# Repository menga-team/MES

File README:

1.  Clone the repository with submodules:
    SSH:
        $ git clone --recursive git@github.com:menga-team/MES.git
    HTTPS:
        $ git clone --recursive https://github.com/menga-team/MES.git
    If you already cloned the repository you can initialize the submodules with following command:
        $ git submodule update --init

2. Make libopencm3:
    $ cd libopencm3
    $ make

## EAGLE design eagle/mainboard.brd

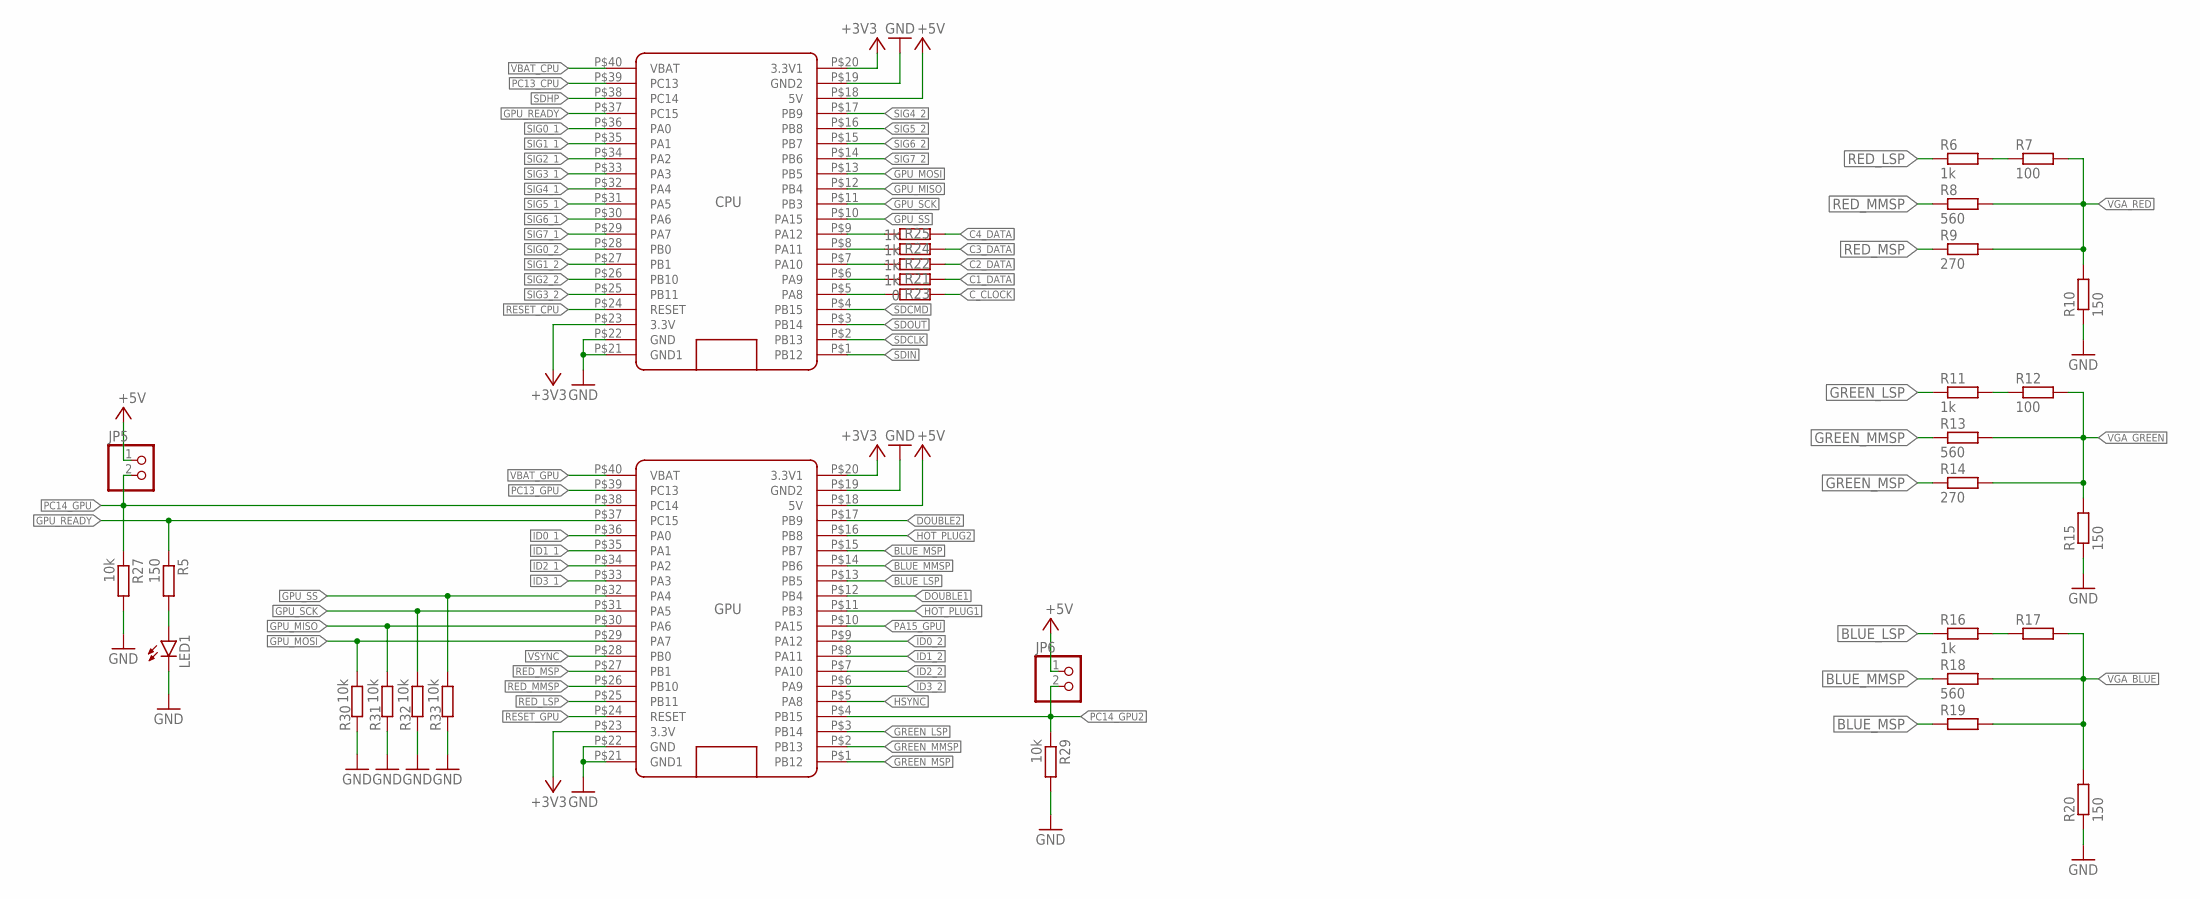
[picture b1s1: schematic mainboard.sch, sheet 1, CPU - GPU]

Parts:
CPU: BLUE_PILLADVANCED; BLUE_PILL_ADV
GPU: BLUE_PILLADVANCED; BLUE_PILL_ADV
JP5, JP6: PINHD-1X2; 1X02
LED1: LEDCHIPLED_0805; CHIPLED_0805
R5, R10, R15, R20: 150; R0805
R6, R11, R16, R21, R22, R24, R25: 1k; R0805
R7, R12, R17: 100; R0805
R8, R13, R18: 560; R0805
R9, R14, R19: 270; R0805
R23: 0; R0805
R27, R29, R30, R31, R32, R33: 10k; R0805

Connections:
+3V3: CPU.P$20 (3.3V1), CPU.P$23 (3.3V), GPU.P$20 (3.3V1), GPU.P$23 (3.3V); also elsewhere on the board
+5V: CPU.P$18 (5V), GPU.P$18 (5V), JP5.1, JP6.1; also elsewhere on the board
BLUE_LSP: GPU.P$13 (PB5), R16.1
BLUE_MMSP: GPU.P$14 (PB6), R18.1
BLUE_MSP: GPU.P$15 (PB7), R19.1
C1_DATA: R21.1; also elsewhere on the board
C2_DATA: R22.1; also elsewhere on the board
C3_DATA: R24.1; also elsewhere on the board
C4_DATA: R25.1; also elsewhere on the board
C_CLOCK: R23.1; also elsewhere on the board
DOUBLE1: GPU.P$12 (PB4); also elsewhere on the board
DOUBLE2: GPU.P$17 (PB9); also elsewhere on the board
GND: CPU.P$19 (GND2), CPU.P$21 (GND1), CPU.P$22 (GND), GPU.P$19 (GND2), GPU.P$21 (GND1), GPU.P$22 (GND), LED1.C, R10.1, R15.1, R20.1, R27.2, R29.2, R30.2, R31.2, R32.2, R33.2; also elsewhere on the board
GPU_MISO: CPU.P$12 (PB4), GPU.P$30 (PA6), R31.1
GPU_MOSI: CPU.P$13 (PB5), GPU.P$29 (PA7), R30.1
GPU_READY: CPU.P$37 (PC15), GPU.P$37 (PC15), R5.1
GPU_SCK: CPU.P$11 (PB3), GPU.P$31 (PA5), R32.1
GPU_SS: CPU.P$10 (PA15), GPU.P$32 (PA4), R33.1
GREEN_LSP: GPU.P$3 (PB14), R11.1
GREEN_MMSP: GPU.P$2 (PB13), R13.1
GREEN_MSP: GPU.P$1 (PB12), R14.1
HOT_PLUG1: GPU.P$11 (PB3); also elsewhere on the board
HOT_PLUG2: GPU.P$16 (PB8); also elsewhere on the board
HSYNC: GPU.P$5 (PA8); also elsewhere on the board
ID0_1: GPU.P$36 (PA0); also elsewhere on the board
ID0_2: GPU.P$9 (PA12); also elsewhere on the board
ID1_1: GPU.P$35 (PA1); also elsewhere on the board
ID1_2: GPU.P$8 (PA11); also elsewhere on the board
ID2_1: GPU.P$34 (PA2); also elsewhere on the board
ID2_2: GPU.P$7 (PA10); also elsewhere on the board
ID3_1: GPU.P$33 (PA3); also elsewhere on the board
ID3_2: GPU.P$6 (PA9); also elsewhere on the board
unnamed: LED1.A, R5.2
unnamed: R6.2, R7.1
unnamed: R11.2, R12.1
unnamed: R16.2, R17.1
PA8_CPU: CPU.P$5 (PA8), R23.2
PA9_CPU: CPU.P$6 (PA9), R21.2
PA9_CPU1: CPU.P$8 (PA11), R24.2
PA10_CPU: CPU.P$7 (PA10), R22.2
PA10_CPU1: CPU.P$9 (PA12), R25.2
PA15_GPU: GPU.P$10 (PA15)
PC13_CPU: CPU.P$39 (PC13)
PC13_GPU: GPU.P$39 (PC13)
PC14_GPU: GPU.P$38 (PC14), JP5.2, R27.1
PC14_GPU2: GPU.P$4 (PB15), JP6.2, R29.1
RED_LSP: GPU.P$25 (PB11), R6.1
RED_MMSP: GPU.P$26 (PB10), R8.1
RED_MSP: GPU.P$27 (PB1), R9.1
RESET_CPU: CPU.P$24 (RESET)
RESET_GPU: GPU.P$24 (RESET)
SDCLK: CPU.P$2 (PB13); also elsewhere on the board
SDCMD: CPU.P$4 (PB15); also elsewhere on the board
SDHP: CPU.P$38 (PC14); also elsewhere on the board
SDIN: CPU.P$1 (PB12); also elsewhere on the board
SDOUT: CPU.P$3 (PB14); also elsewhere on the board
SIG0_1: CPU.P$36 (PA0); also elsewhere on the board
SIG0_2: CPU.P$28 (PB0); also elsewhere on the board
SIG1_1: CPU.P$35 (PA1); also elsewhere on the board
SIG1_2: CPU.P$27 (PB1); also elsewhere on the board
SIG2_1: CPU.P$34 (PA2); also elsewhere on the board
SIG2_2: CPU.P$26 (PB10); also elsewhere on the board
SIG3_1: CPU.P$33 (PA3); also elsewhere on the board
SIG3_2: CPU.P$25 (PB11); also elsewhere on the board
SIG4_1: CPU.P$32 (PA4); also elsewhere on the board
SIG4_2: CPU.P$17 (PB9); also elsewhere on the board
SIG5_1: CPU.P$31 (PA5); also elsewhere on the board
SIG5_2: CPU.P$16 (PB8); also elsewhere on the board
SIG6_1: CPU.P$30 (PA6); also elsewhere on the board
SIG6_2: CPU.P$15 (PB7); also elsewhere on the board
SIG7_1: CPU.P$29 (PA7); also elsewhere on the board
SIG7_2: CPU.P$14 (PB6); also elsewhere on the board
VBAT_CPU: CPU.P$40 (VBAT)
VBAT_GPU: GPU.P$40 (VBAT)
VGA_BLUE: R17.2, R18.2, R19.2, R20.2; also elsewhere on the board
VGA_GREEN: R12.2, R13.2, R14.2, R15.2; also elsewhere on the board
VGA_RED: R7.2, R8.2, R9.2, R10.2; also elsewhere on the board
VSYNC: GPU.P$28 (PB0); also elsewhere on the board

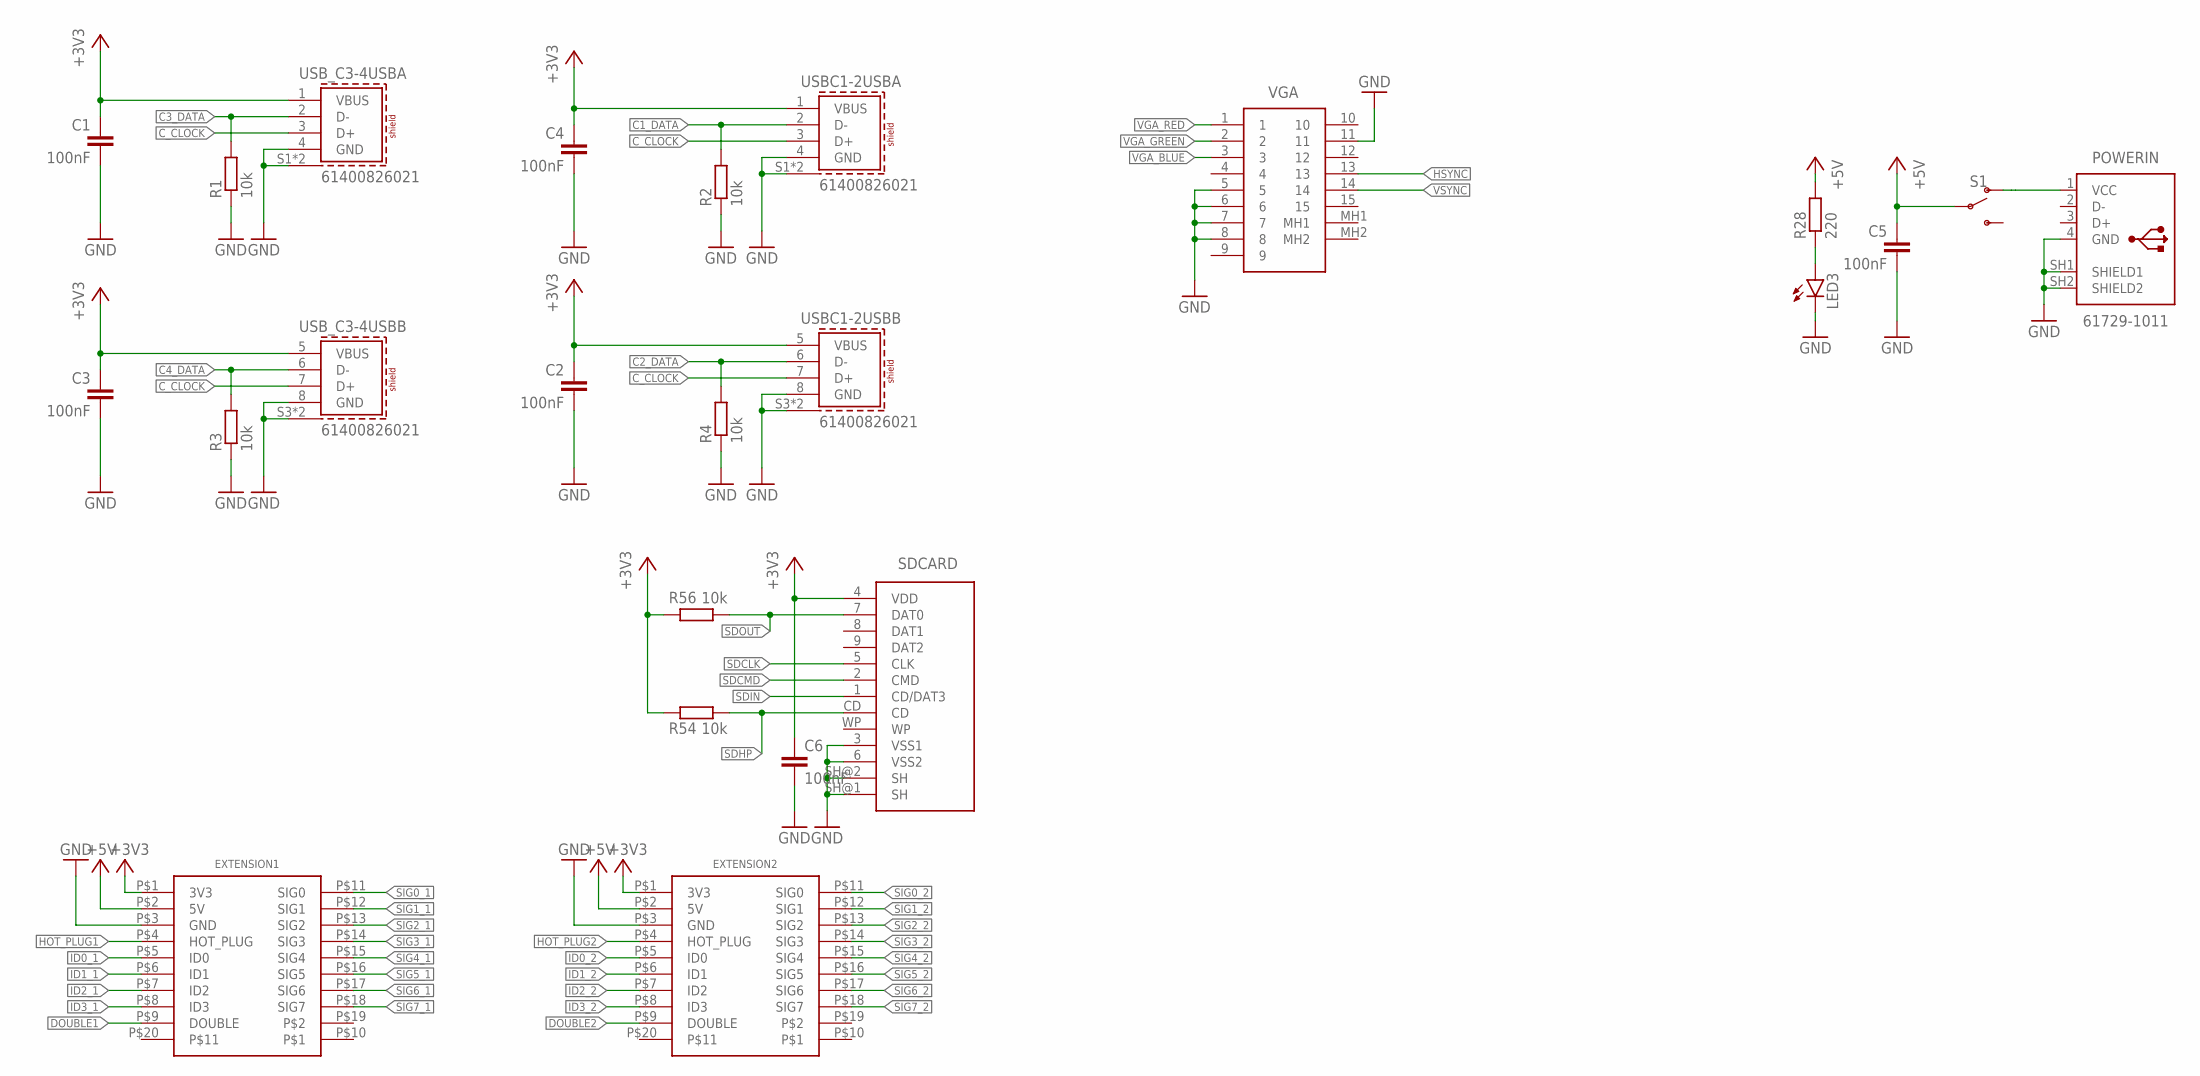
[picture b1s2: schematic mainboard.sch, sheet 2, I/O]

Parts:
C1, C2, C3, C4, C5, C6: 100nF; C0805
EXTENSION1, EXTENSION2: 3511220BMSS0BNA1_2.54MM_2X20_MALE
LED3: LEDCHIPLED_0805; CHIPLED_0805
POWERIN: 61729-1011; 61729-1011BLF
R1, R2, R3, R4, R54, R56: 10k; R0805
R28: 220; R0805
S1: SWITCH-SPDT-PTH-11.6X4.0MM; SWITCH_SPDT_PTH_11.6X4.0MM
SD-CARD: SD_CARD_SOCKET; SD
USBC1-2: 61400826021
USB_C3-4: 61400826021
VGA: L77HDE15SD1CH4RHNVGA

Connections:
+3V3: C1.1, C2.1, C3.1, C4.1, C6.1, EXTENSION1.P$1 (3V3), EXTENSION2.P$1 (3V3), R54.2, R56.2, SD-CARD.4 (VDD), USBC1-2.1 (VBUS), USBC1-2.5 (VBUS), USB_C3-4.1 (VBUS), USB_C3-4.5 (VBUS); also elsewhere on the board
+5V: C5.1, EXTENSION1.P$2 (5V), EXTENSION2.P$2 (5V), R28.2, S1.2; also elsewhere on the board
C1_DATA: R2.2, USBC1-2.2 (D-); also elsewhere on the board
C2_DATA: R4.2, USBC1-2.6 (D-); also elsewhere on the board
C3_DATA: R1.2, USB_C3-4.2 (D-); also elsewhere on the board
C4_DATA: R3.2, USB_C3-4.6 (D-); also elsewhere on the board
C_CLOCK: USBC1-2.3 (D+), USBC1-2.7 (D+), USB_C3-4.3 (D+), USB_C3-4.7 (D+); also elsewhere on the board
DOUBLE1: EXTENSION1.P$9 (DOUBLE); also elsewhere on the board
DOUBLE2: EXTENSION2.P$9 (DOUBLE); also elsewhere on the board
GND: C1.2, C2.2, C3.2, C4.2, C5.2, C6.2, EXTENSION1.P$3 (GND), EXTENSION2.P$3 (GND), LED3.C, POWERIN.4 (GND), POWERIN.SH1 (SHIELD1), POWERIN.SH2 (SHIELD2), R1.1, R2.1, R3.1, R4.1, SD-CARD.3 (VSS1), SD-CARD.6 (VSS2), SD-CARD.SH@1 (SH), SD-CARD.SH@2 (SH), USBC1-2.4 (GND), USBC1-2.8 (GND), USBC1-2.S1 (SHIELD), USBC1-2.S2 (SHIELD), USBC1-2.S3 (SHIELD), USBC1-2.S4 (SHIELD), USB_C3-4.4 (GND), USB_C3-4.8 (GND), USB_C3-4.S1 (SHIELD), USB_C3-4.S2 (SHIELD), USB_C3-4.S3 (SHIELD), USB_C3-4.S4 (SHIELD), VGA.5, VGA.6, VGA.7, VGA.8, VGA.11; also elsewhere on the board
HOT_PLUG1: EXTENSION1.P$4 (HOT_PLUG); also elsewhere on the board
HOT_PLUG2: EXTENSION2.P$4 (HOT_PLUG); also elsewhere on the board
HSYNC: VGA.13; also elsewhere on the board
ID0_1: EXTENSION1.P$5 (ID0); also elsewhere on the board
ID0_2: EXTENSION2.P$5 (ID0); also elsewhere on the board
ID1_1: EXTENSION1.P$6 (ID1); also elsewhere on the board
ID1_2: EXTENSION2.P$6 (ID1); also elsewhere on the board
ID2_1: EXTENSION1.P$7 (ID2); also elsewhere on the board
ID2_2: EXTENSION2.P$7 (ID2); also elsewhere on the board
ID3_1: EXTENSION1.P$8 (ID3); also elsewhere on the board
ID3_2: EXTENSION2.P$8 (ID3); also elsewhere on the board
unnamed: POWERIN.1 (VCC), S1.1 (O)
unnamed: LED3.A, R28.1
SDCLK: SD-CARD.5 (CLK); also elsewhere on the board
SDCMD: SD-CARD.2 (CMD); also elsewhere on the board
SDHP: R54.1, SD-CARD.CD; also elsewhere on the board
SDIN: SD-CARD.1 (CD/DAT3); also elsewhere on the board
SDOUT: R56.1, SD-CARD.7 (DAT0); also elsewhere on the board
SIG0_1: EXTENSION1.P$11 (SIG0); also elsewhere on the board
SIG0_2: EXTENSION2.P$11 (SIG0); also elsewhere on the board
SIG1_1: EXTENSION1.P$12 (SIG1); also elsewhere on the board
SIG1_2: EXTENSION2.P$12 (SIG1); also elsewhere on the board
SIG2_1: EXTENSION1.P$13 (SIG2); also elsewhere on the board
SIG2_2: EXTENSION2.P$13 (SIG2); also elsewhere on the board
SIG3_1: EXTENSION1.P$14 (SIG3); also elsewhere on the board
SIG3_2: EXTENSION2.P$14 (SIG3); also elsewhere on the board
SIG4_1: EXTENSION1.P$15 (SIG4); also elsewhere on the board
SIG4_2: EXTENSION2.P$15 (SIG4); also elsewhere on the board
SIG5_1: EXTENSION1.P$16 (SIG5); also elsewhere on the board
SIG5_2: EXTENSION2.P$16 (SIG5); also elsewhere on the board
SIG6_1: EXTENSION1.P$17 (SIG6); also elsewhere on the board
SIG6_2: EXTENSION2.P$17 (SIG6); also elsewhere on the board
SIG7_1: EXTENSION1.P$18 (SIG7); also elsewhere on the board
SIG7_2: EXTENSION2.P$18 (SIG7); also elsewhere on the board
VGA_BLUE: VGA.3; also elsewhere on the board
VGA_GREEN: VGA.2; also elsewhere on the board
VGA_RED: VGA.1; also elsewhere on the board
VSYNC: VGA.14; also elsewhere on the board

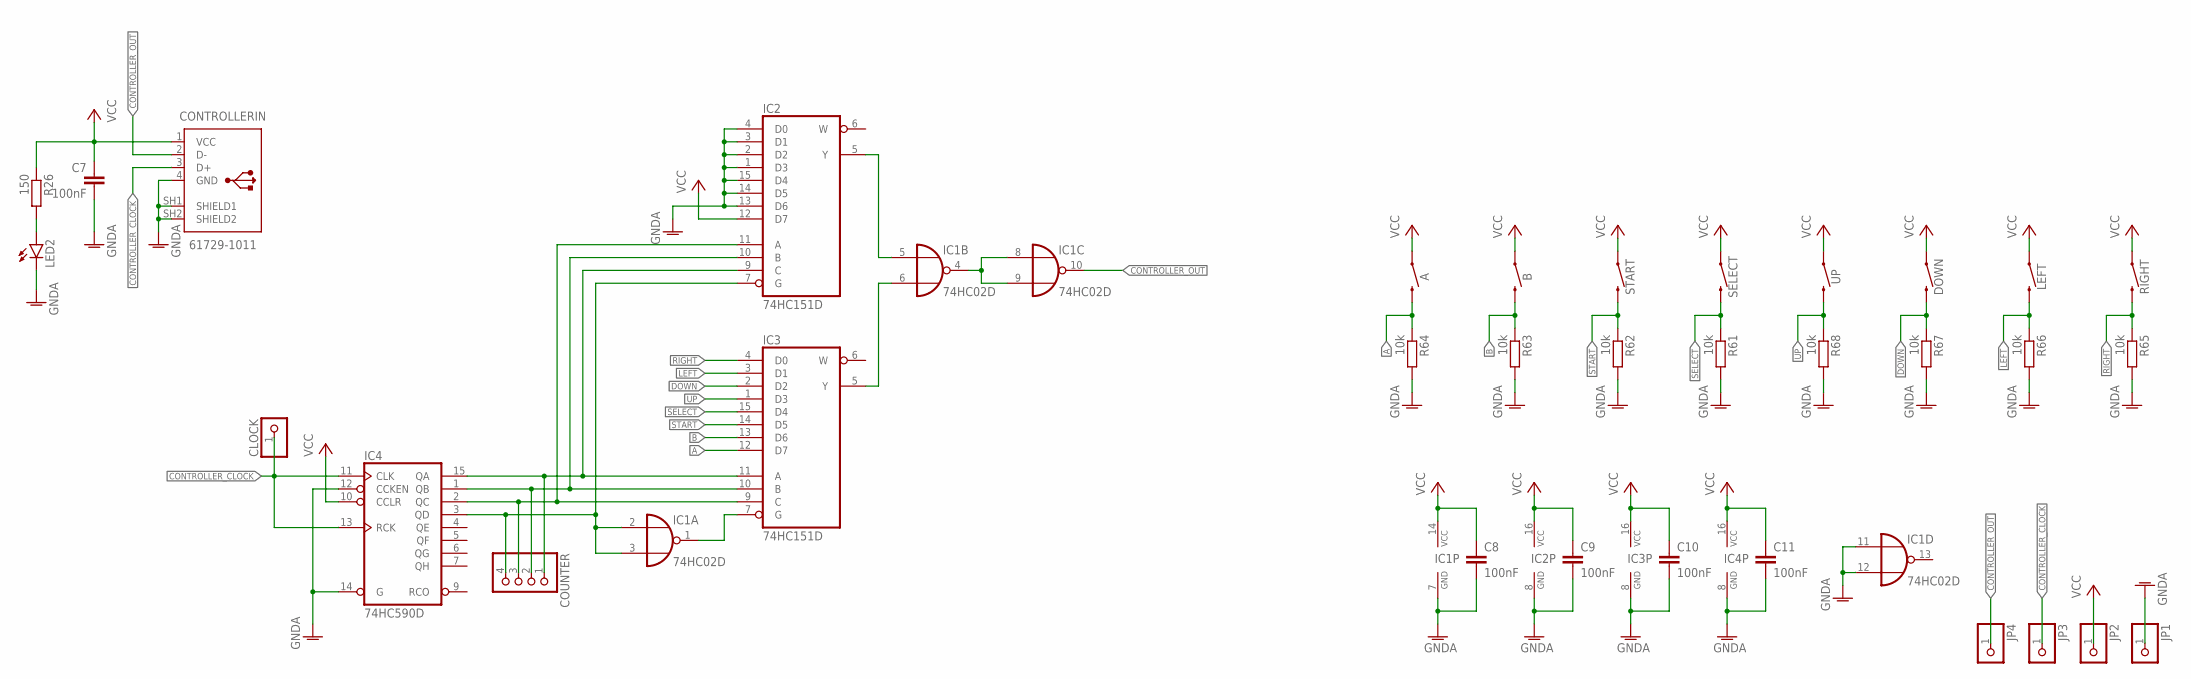
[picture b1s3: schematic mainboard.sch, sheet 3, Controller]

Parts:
A: MOMENTARY-SWITCH-SPST-PTH-12MM; TACTILE_SWITCH_PTH_12MM
B: MOMENTARY-SWITCH-SPST-PTH-12MM; TACTILE_SWITCH_PTH_12MM
C7, C8, C9, C10, C11: 100nF; C0805
CLOCK: PINHD-1X1; 1X01
CONTROLLERIN: 61729-1011; 61729-1011BLF
COUNTER: PINHD-1X4; 1X04
DOWN: MOMENTARY-SWITCH-SPST-PTH-12MM; TACTILE_SWITCH_PTH_12MM
IC1: 74HC02D; SO14
IC2, IC3: 74HC151D; SO16
IC4: 74HC590D; SO16
JP1, JP2, JP3, JP4: PINHD-1X1; 1X01
LED2: LEDCHIPLED_0805; CHIPLED_0805
LEFT: MOMENTARY-SWITCH-SPST-PTH-12MM; TACTILE_SWITCH_PTH_12MM
R26: 150; R0805
R61, R62, R63, R64, R65, R66, R67, R68: 10k; R0805
RIGHT: MOMENTARY-SWITCH-SPST-PTH-12MM; TACTILE_SWITCH_PTH_12MM
SELECT: MOMENTARY-SWITCH-SPST-PTH-12MM; TACTILE_SWITCH_PTH_12MM
START: MOMENTARY-SWITCH-SPST-PTH-12MM; TACTILE_SWITCH_PTH_12MM
UP: MOMENTARY-SWITCH-SPST-PTH-12MM; TACTILE_SWITCH_PTH_12MM

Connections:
A: A.3 (2), IC3.12 (D7), R64.1
B: B.3 (2), IC3.13 (D6), R63.1
CONTROLLER_CLOCK: CLOCK.1, CONTROLLERIN.3 (D+), IC4.11 (CLK), IC4.13 (RCK), JP3.1
CONTROLLER_OUT: CONTROLLERIN.2 (D-), IC1.10 (O), JP4.1
DOWN: DOWN.3 (2), IC3.2 (D2), R67.1
GNDA: C7.2, C8.2, C9.2, C10.2, C11.2, CONTROLLERIN.4 (GND), CONTROLLERIN.SH1 (SHIELD1), CONTROLLERIN.SH2 (SHIELD2), IC1.7 (GND), IC1.11 (I0), IC1.12 (I1), IC2.1 (D3), IC2.2 (D2), IC2.3 (D1), IC2.4 (D0), IC2.8 (GND), IC2.13 (D6), IC2.14 (D5), IC2.15 (D4), IC3.8 (GND), IC4.8 (GND), IC4.12 (CCKEN), IC4.14 (G), JP1.1, LED2.C, R61.2, R62.2, R63.2, R64.2, R65.2, R66.2, R67.2, R68.2
LEFT: IC3.3 (D1), LEFT.3 (2), R66.1
unnamed: LED2.A, R26.2
unnamed: IC1.5 (I0), IC2.5 (Y)
unnamed: IC1.6 (I1), IC3.5 (Y)
unnamed: IC1.4 (O), IC1.8 (I0), IC1.9 (I1)
unnamed: COUNTER.1, IC2.9 (C), IC3.11 (A), IC4.15 (QA)
unnamed: COUNTER.2, IC2.10 (B), IC3.10 (B), IC4.1 (QB)
unnamed: COUNTER.3, IC2.11 (A), IC3.9 (C), IC4.2 (QC)
unnamed: COUNTER.4, IC1.2 (I0), IC1.3 (I1), IC2.7 (G), IC4.3 (QD)
unnamed: IC1.1 (O), IC3.7 (G)
RIGHT: IC3.4 (D0), R65.1, RIGHT.3 (2)
SELECT: IC3.15 (D4), R61.1, SELECT.3 (2)
START: IC3.14 (D5), R62.1, START.3 (2)
UP: IC3.1 (D3), R68.1, UP.3 (2)
VCC: A.1, B.1, C7.1, C8.1, C9.1, C10.1, C11.1, CONTROLLERIN.1 (VCC), DOWN.1, IC1.14 (VCC), IC2.12 (D7), IC2.16 (VCC), IC3.16 (VCC), IC4.10 (CCLR), IC4.16 (VCC), JP2.1, LEFT.1, R26.1, RIGHT.1, SELECT.1, START.1, UP.1

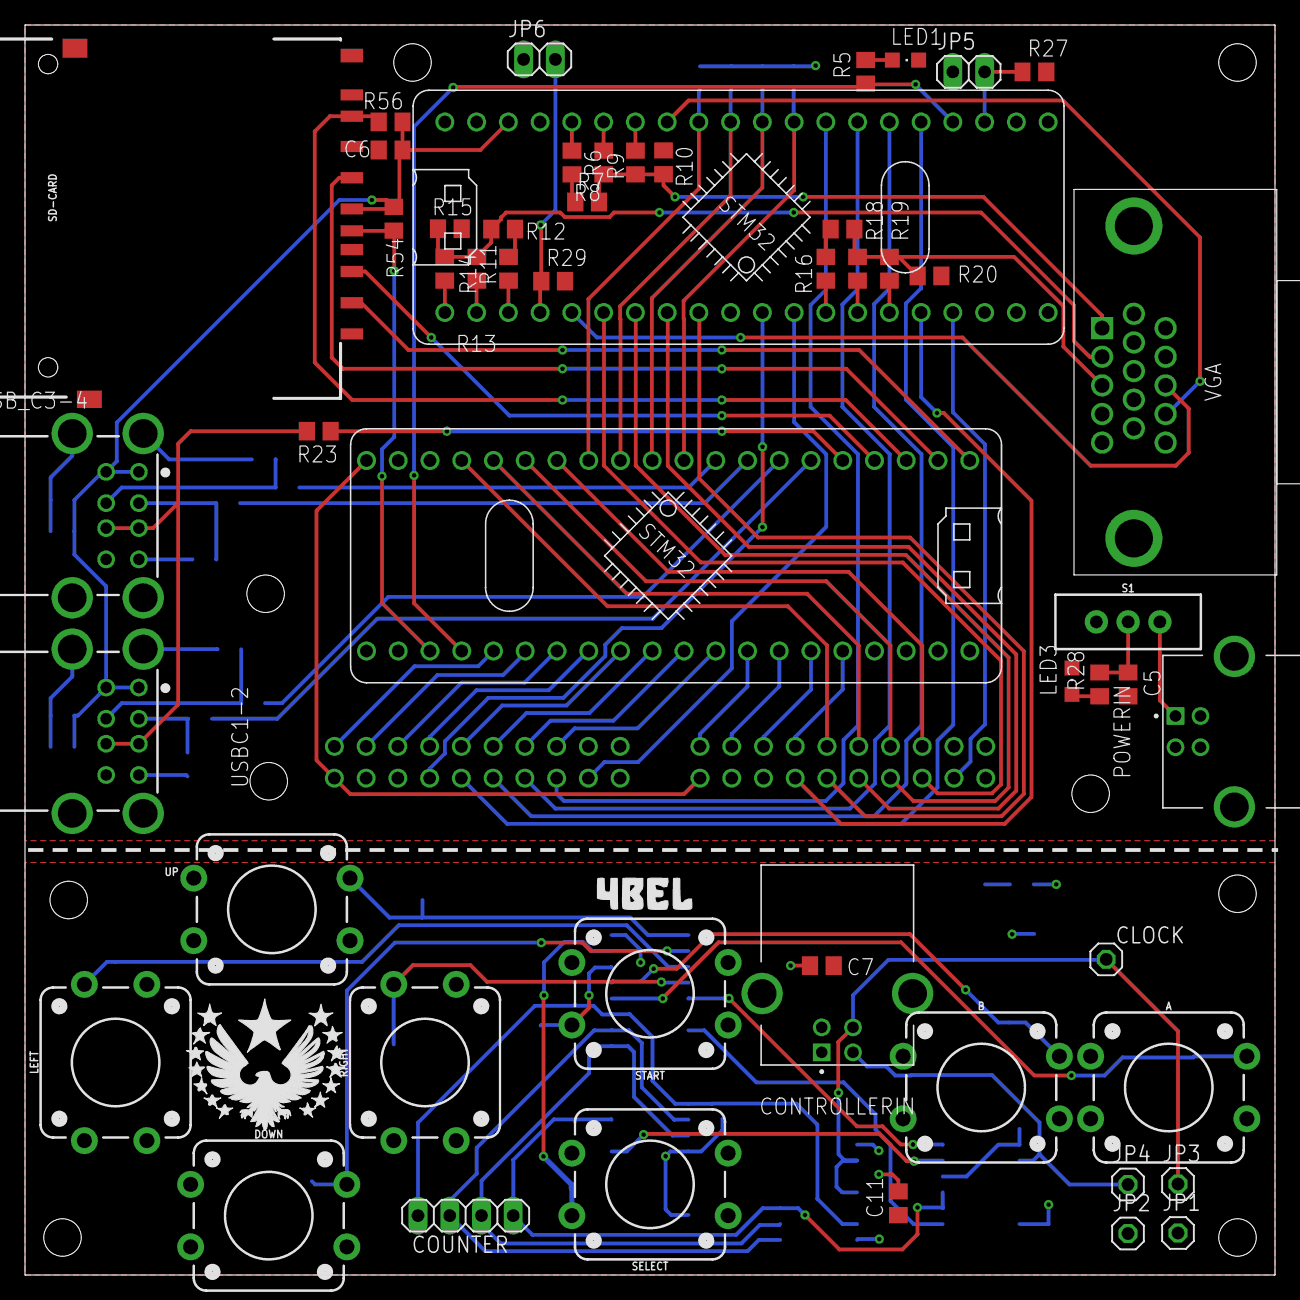
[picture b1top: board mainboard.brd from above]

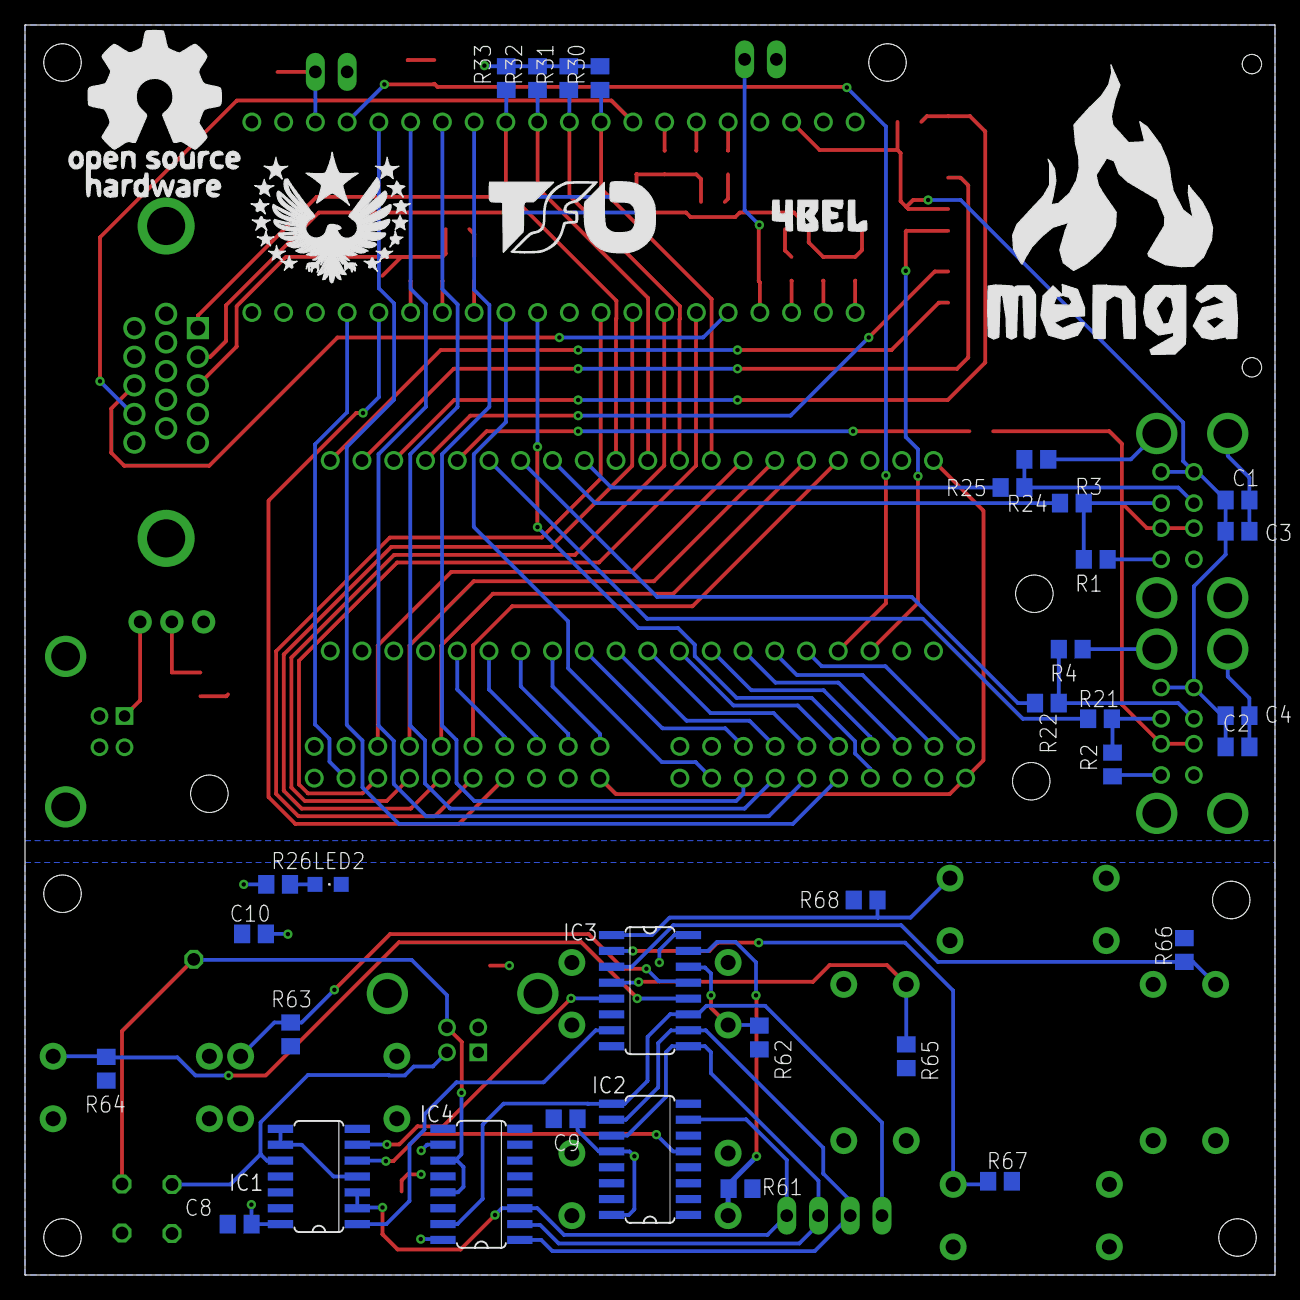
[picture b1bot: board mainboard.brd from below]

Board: 2 copper layers, 100.0 x 100.0 mm, 88 parts (33 on the bottom side), 94 nets.

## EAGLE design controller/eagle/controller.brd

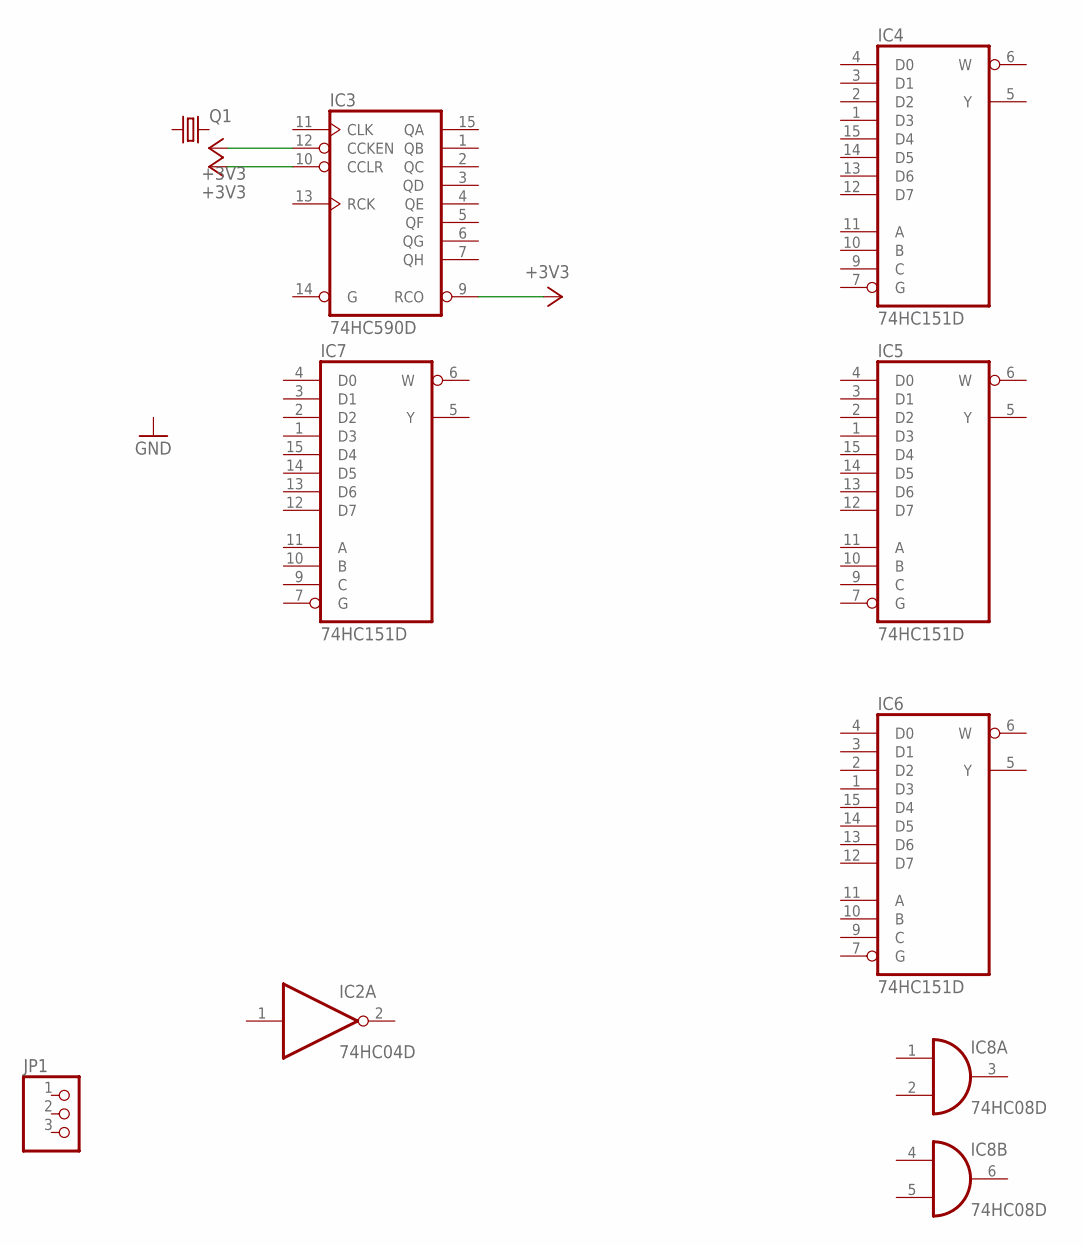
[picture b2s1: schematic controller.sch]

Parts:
IC2: 74HC04D; SO14
IC3: 74HC590D; SO16
IC4, IC5, IC6, IC7: 74HC151D; SO16
IC8: 74HC08D; SO14
JP1: PINHD-1X3/90; 1X03/90
Q1: CRYSTAL68SMX; 86SMX

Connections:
+3V3: IC3.9 (RCO), IC3.10 (CCLR), IC3.12 (CCKEN)
GND: IC2.7 (GND), IC3.8 (GND), IC4.8 (GND), IC5.8 (GND), IC6.8 (GND), IC7.8 (GND), IC8.7 (GND)
VCC: IC2.14 (VCC), IC3.16 (VCC), IC4.16 (VCC), IC5.16 (VCC), IC6.16 (VCC), IC7.16 (VCC), IC8.14 (VCC)

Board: 2 copper layers, 9 parts (0 on the bottom side), 3 nets, no tracks yet.

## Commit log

2022-09-10 GPU dokumentation
2022-09-14 setup makefile
2022-09-14 fix make file
2022-09-14 wrong rom size
2022-09-15 start with vga sync
2022-09-15 refactoring & make compile
2022-09-16 second controller blueprint
2022-09-17 implement vga sync
2022-09-19 third controller blueprint
2022-09-21 reworked controller :(
2022-09-23 update simulation image
2022-09-30 vga out works (again)
2022-10-01 optimize code a little bit
2022-10-05 inbuilt-led test
2022-10-05 controller
2022-10-05 file structure
2022-10-05 optimization wip
2022-10-06 bug in video buffer (and maybe tim3?)
2022-10-08 fix buffer + improve performance
2022-10-08 trying out various techniques for getting pixel sizes correct
2022-10-10 eagle setup
2022-10-14 acceptable ig 🤷
2022-10-14 controller board with eagle
2022-10-19 usb type b
2022-10-19 cpu folder push
2022-10-20 move sim_rasp to ../simulations
2022-10-21 create mainboard scematic
2022-10-23 add usb type c
2022-10-24 first sound generation test
2022-10-28 new usb controller stuff
2022-10-29 change pixel format & create tool for converting images
2022-10-29 fix scanline size & various improvments
2022-10-31 start with cpu-gpu communication
2022-10-31 make tests readme more accessible
2022-10-31 I/O's
2022-11-01 implement systick and reorganize cpu project
2022-11-01 begin with cpu-gpu communication
2022-11-01 implement 1bit palette encoding
2022-11-01 finish controller refactor
2022-11-01 create gpu module
2022-11-01 refactor makefiles
2022-11-01 refactor gpu
2022-11-10 support 9-bit color
2022-11-10 add extern variables to controller.h
2022-11-11 testing...
2022-11-12 add basic cpu-gpu communication
2022-11-12 gpu: implement more flexible processing pipeline
2022-11-13 gpu: various improvments
2022-11-13 implement converting of 2bpp indexed-pngs
2022-11-17 very small changes
2022-11-18 gpu: implement more operations
2022-11-18 add new font
2022-11-18 vandi commit
2022-11-22 initial sd-card support
2022-11-22 implemented function in wrong file
2022-11-23 font
2022-11-23 partial support for reading blocks
2022-11-23 added mainboard controller logic
2022-11-25 mainboard controller schematic
2022-11-26 implement writing sectors
2022-11-26 send gpu data via dma instead of blocking
2022-11-26 generate font automatically
2022-12-01 replaced usb-c 24 pin reciver with 12 pin reciver
2022-12-02 updated font
2022-12-02 fixed font
2022-12-02 fixed font again
2022-12-02 seperate internal methods from user methods
2022-12-02 refactored and divided in internal and external controller
2022-12-17 don't compile controller
2022-12-17 pyqt5 script to emulate a controller using an arduino (UNO)
2022-12-17 added nice pic that explains the keyboard layout of the controller emulator
2022-12-19 support sdsc
2022-12-19 fix readme
2022-12-19 fix text overlapping
2022-12-21 improve communication on gpu side
2022-12-22 improve gpu performance
2022-12-23 implement cpu timeout and cleanup
2022-12-23 2nd reset before giving up if first failed
2022-12-24 improved controller emulator
2022-12-24 update to new specification
2022-12-24 deleted vga.sch and updated eagle library
2022-12-25 add demo game
2022-12-25 more communication
2023-01-18 updated USB-C receptacles and würth library
2023-01-18 renamed the pins for CPU and GPU
2023-01-18 relocate buffer into userspace api
2023-01-18 rename time module
2023-01-18 update games to reflect changes in timer module
2023-01-18 cleaned up schemtic
2023-01-18 added Board to board connector
2023-01-18 nonzero amount of refactoring
2023-01-18 add function for swapping buffers
2023-01-18 free allocated buffers when error occurs
2023-01-20 working on game loading
2023-01-20 fixed schematic
2023-01-22 new controller logic implemented
2023-01-22 first forking draft for game loading
2023-01-22 Fix buffer alloc and buffer_get_pixel
2023-01-22 fixed alloc (again)
2023-01-22 erc check
2023-01-23 fixed controller.sch
2023-01-25 changed usb-c pin used by controller
2023-01-25 changed connector library ad wired up to cpu/gpu
2023-01-25 wired sd card slot
2023-01-26 new controller software
2023-01-27 finalized schematik with detommaso and spiss supervision
2023-01-27 updated controller simulator to new komunikation protokoll
2023-02-09 initial work towards making communication artifact-less
2023-02-12 reimplement gpu ready & switch to 640x480@60
2023-02-12 update cpu according to new gpu ready behaviour
2023-02-13 Schematic V1
2023-02-15 Schematic complete
2023-02-24 fixing local symbols in multiple files when compiling module.
    Reformat everything with the new style
2023-02-24 forgot to commit symbol extractor
2023-02-24 make example game work
2023-03-10 add note to cpu
2023-03-14 Board almost finished
2023-03-17 update to newest codebase
2023-03-18 fix image cut off edge case
2023-03-18 set board labels and fixed errors
2023-03-18 added License (sry vlad)
2023-03-18 make game testing easier
2023-03-18 fix again
2023-03-18 implement flashing with game, and fix fpn.
2023-03-18 forgot aeabi.h
2023-03-19 added fancy drawings and logos on the back of the board
2023-03-19 startup animation
2023-03-19 some drc improvements
2023-03-19 fixed errors, rewired controller clock and fixed buttons on wrong layer
2023-03-19 smoother timing
2023-03-20 huber approve check has been given
2023-03-20 usb change
2023-03-20 implement more operations
2023-03-21 board changes
2023-03-21 positioned controller reciver, massive cleanup, simplified routes, moved labels
2023-03-26 implement everything needed for creating icons
    this utility has become cluttered...
2023-03-29 start with sdformat program
2023-04-01 add rng to cpu
2023-04-01 clean up
2023-04-01 typo
2023-04-03 complete iso creation
2023-04-03 implement more errors
2023-04-08 implement dd-like functionality
2023-04-10 add revision system
2023-04-10 test
2023-04-13 use error messages from udynlink
2023-04-13 small improvements
2023-04-13 add some more symbols
2023-04-13 print unknown symbol
2023-04-14 Work in progress board rework
2023-04-14 more timing methods
2023-04-14 better hardfault message
2023-04-15 update software to match board
2023-04-15 implement controller (input.h)
2023-04-15 fix symbols
2023-04-15 reset palette when reconnecting
2023-04-15 symbols...
2023-04-16 add realloc
2023-04-16 make gpu operation data larger
2023-04-16 implement controller into the gui
2023-04-19 design changes
2023-04-21 check for invalid controller signal
2023-04-21 pcb v2
2023-04-21 pcb: gpu ready led
2023-04-26 made D-pad quadrtatic, corrected other minor stuff
2023-04-26 update udynlink
2023-04-26 exclude last_port
2023-04-26 exclude more symbols that appear after flashing a game
2023-04-27 added svg art and finished todo list
2023-04-28 macos symbols
2023-04-28 write game image to seperate section
2023-04-28 fix all warnings when compiling cpu
2023-05-03 pcb: v2 features
2023-05-03 huber approved pcb 2.0
2023-05-04 for the lazy people
2023-05-06 fix memory layout
2023-05-06 implement loading external games
2023-05-07 bug fixes
2023-05-07 fix flashing
2023-05-07 fix compiling game with firmware
2023-05-07 fix small memory leaks
2023-05-07 qol changes
2023-05-07 run flashed game if cpu was reset and gpu is already initialized.
2023-05-07 support spec 1.0 sd cards
2023-05-12 expand rom space
2023-05-12 wrong artifact path
2023-05-12 use regular apt-get
2023-05-12 fix hcxc detection
2023-05-12 implement data.h
2023-05-12 forgot to add files
2023-05-17 improved font
2023-05-17 fix font stuff
2023-05-21 make clock polarity = 0
2023-05-27 update gpu docs
2023-06-05 add more symbols
2023-06-05 add another
2023-06-13 implement new data function
2023-06-18 fix data
2023-06-18 fix ci (maybe)
2023-06-18 ubuntu too outdated?
2023-06-18 fix yaml
2023-06-18 forgot dependencies
2023-06-18 use checkout instead of running command
2023-06-18 use python3 instead of python
2024-04-04 sdcard: Fix the CRC16 algorithm.
2024-04-07 sdcard: remove unnecessary goto

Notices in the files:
parts and their libraries:
Eagle_WR-USB: Copyright: Würth Elektronik
SparkFun-Switches: Licensing: Creative Commons ShareAlike 4.0 International - https://creativecommons.org/licenses/by-sa/4.0
